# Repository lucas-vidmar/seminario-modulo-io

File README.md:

# Módulo Input / Output (I/O) para entornos educativos

> **Autores:**
> - [Lucas Vidmar](https://github.com/lucas-vidmar)
> - [Joaquín Bergmann](https://github.com/JoacoBerg)
> - [Lucas Boiero](https://github.com/boierito)
>
> **Institución:**
> - [Universidad Argentina de la Empresa (UADE)](https://www.uade.edu.ar/)

## Descripción

Este proyecto consiste en un módulo de entrada/salida (I/O) para entornos educativos, que permite a los estudiantes interactuar con sensores y actuadores a través de una interfaz gráfica de usuario (GUI) en un navegador web. El módulo I/O se comunica con el microcontrolador a través de una interfaz I2C, y proporciona una API RESTful para controlar los pines GPIO, los convertidores analógico-digital (ADC) y digital-analógico (DAC), y los codificadores rotatorios.

## Diseño de hardware

### Pinout

| Label | GPIO | Input/Output | Pines utilizados | Modo  |
|-------|------|--------------|------------------|-------|
| D2    | 2    | I/O          | Pantalla         | CS    |
| D4    | 4    | I/O          | PWM              | PWM   |
| D5    | 5    | I/O          | PWM              | PWM   |
| D12   | 12   | I/O          | Encoder          | CLK   |
| D13   | 13   | I/O          | Encoder          | DT    |
| D14   | 14   | I/O          | Encoder          | SW    |
| D15   | 15   | I/O          | DO               | DO    |
| RX2   | 16   | I/O          | U2_RXD           | U2_RXD|
| TX2   | 17   | I/O          | U2_TXD           | U2_TXD|
| D18   | 18   | I/O          | Pantalla         | SCK   |
| D19   | 19   | I/O          | Pantalla         | MISO  |
| D21   | 21   | I/O          | I2C              | SDA   |
| D22   | 22   | I/O          | I2C              | SLC   |
| D23   | 23   | I/O          | Pantalla         | MOSI  |
| D26   | 26   | I/O          | DI               | DI    |
| D27   | 27   | I/O          | DI               | DI    |
| D32   | 32   | I/O          | DO               | DO    |
| D33   | 33   | I/O          | DO               | DO    |
| D34   | 34   | I            | ADC interno      | ADC   |
| D35   | 35   | I            | ADC interno      | ADC   |
| VP    | 36   | I            | DI               | DI    |

### [Esquemático](kicad/Modulo%20IO%20Seminario.kicad_sch)

### [PCB](kicad/Modulo%20IO%20Seminario.kicad_pcb)

## Documentación de código

### [main.h](include/main.h)
Este archivo contiene las declaraciones principales del proyecto, incluidas las declaraciones de funciones para los manejadores de HTML, la impresión de menús, la lógica FSM y el control de GPIO.

### [led.h](include/led.h)
Este archivo contiene la declaración de la clase `BuiltInLed`, que proporciona métodos para controlar el LED incorporado en un microcontrolador.

### [lcdsim.h](include/lcdsim.h)
Este archivo contiene la declaración de la clase `SimulatedLCD`, que simula una pantalla LCD para fines de prueba.

### [i2c.h](include/i2c.h)
Este archivo contiene la declaración de la clase `I2C`, que proporciona métodos para inicializar la interfaz I2C y realizar operaciones de lectura y escritura en el bus I2C.

### [gpio.h](include/gpio.h)
Este archivo contiene la declaración de la clase `GPIO` y sus clases derivadas `DigitalGPIO` y `AnalogGPIO`, que proporcionan métodos para configurar, leer y escribir en los pines GPIO.

### [encodersim.h](include/encodersim.h)
Este archivo contiene la declaración de la clase `SimulatedEncoder`, que simula un codificador para fines de prueba.

### [encoder.h](include/encoder.h)
Este archivo contiene la declaración de la clase `Encoder`, que proporciona métodos para interactuar con un codificador rotatorio.

### [dac.h](include/dac.h)
Este archivo contiene la declaración de la clase `DAC`, que proporciona métodos para inicializar y controlar un Convertidor Digital a Analógico (DAC) a través de I2C.

### [adc.h](include/adc.h)
Este archivo contiene la declaración de la clase `ADC`, que proporciona métodos para interactuar con un Convertidor Analógico a Digital (ADC) a través de I2C.

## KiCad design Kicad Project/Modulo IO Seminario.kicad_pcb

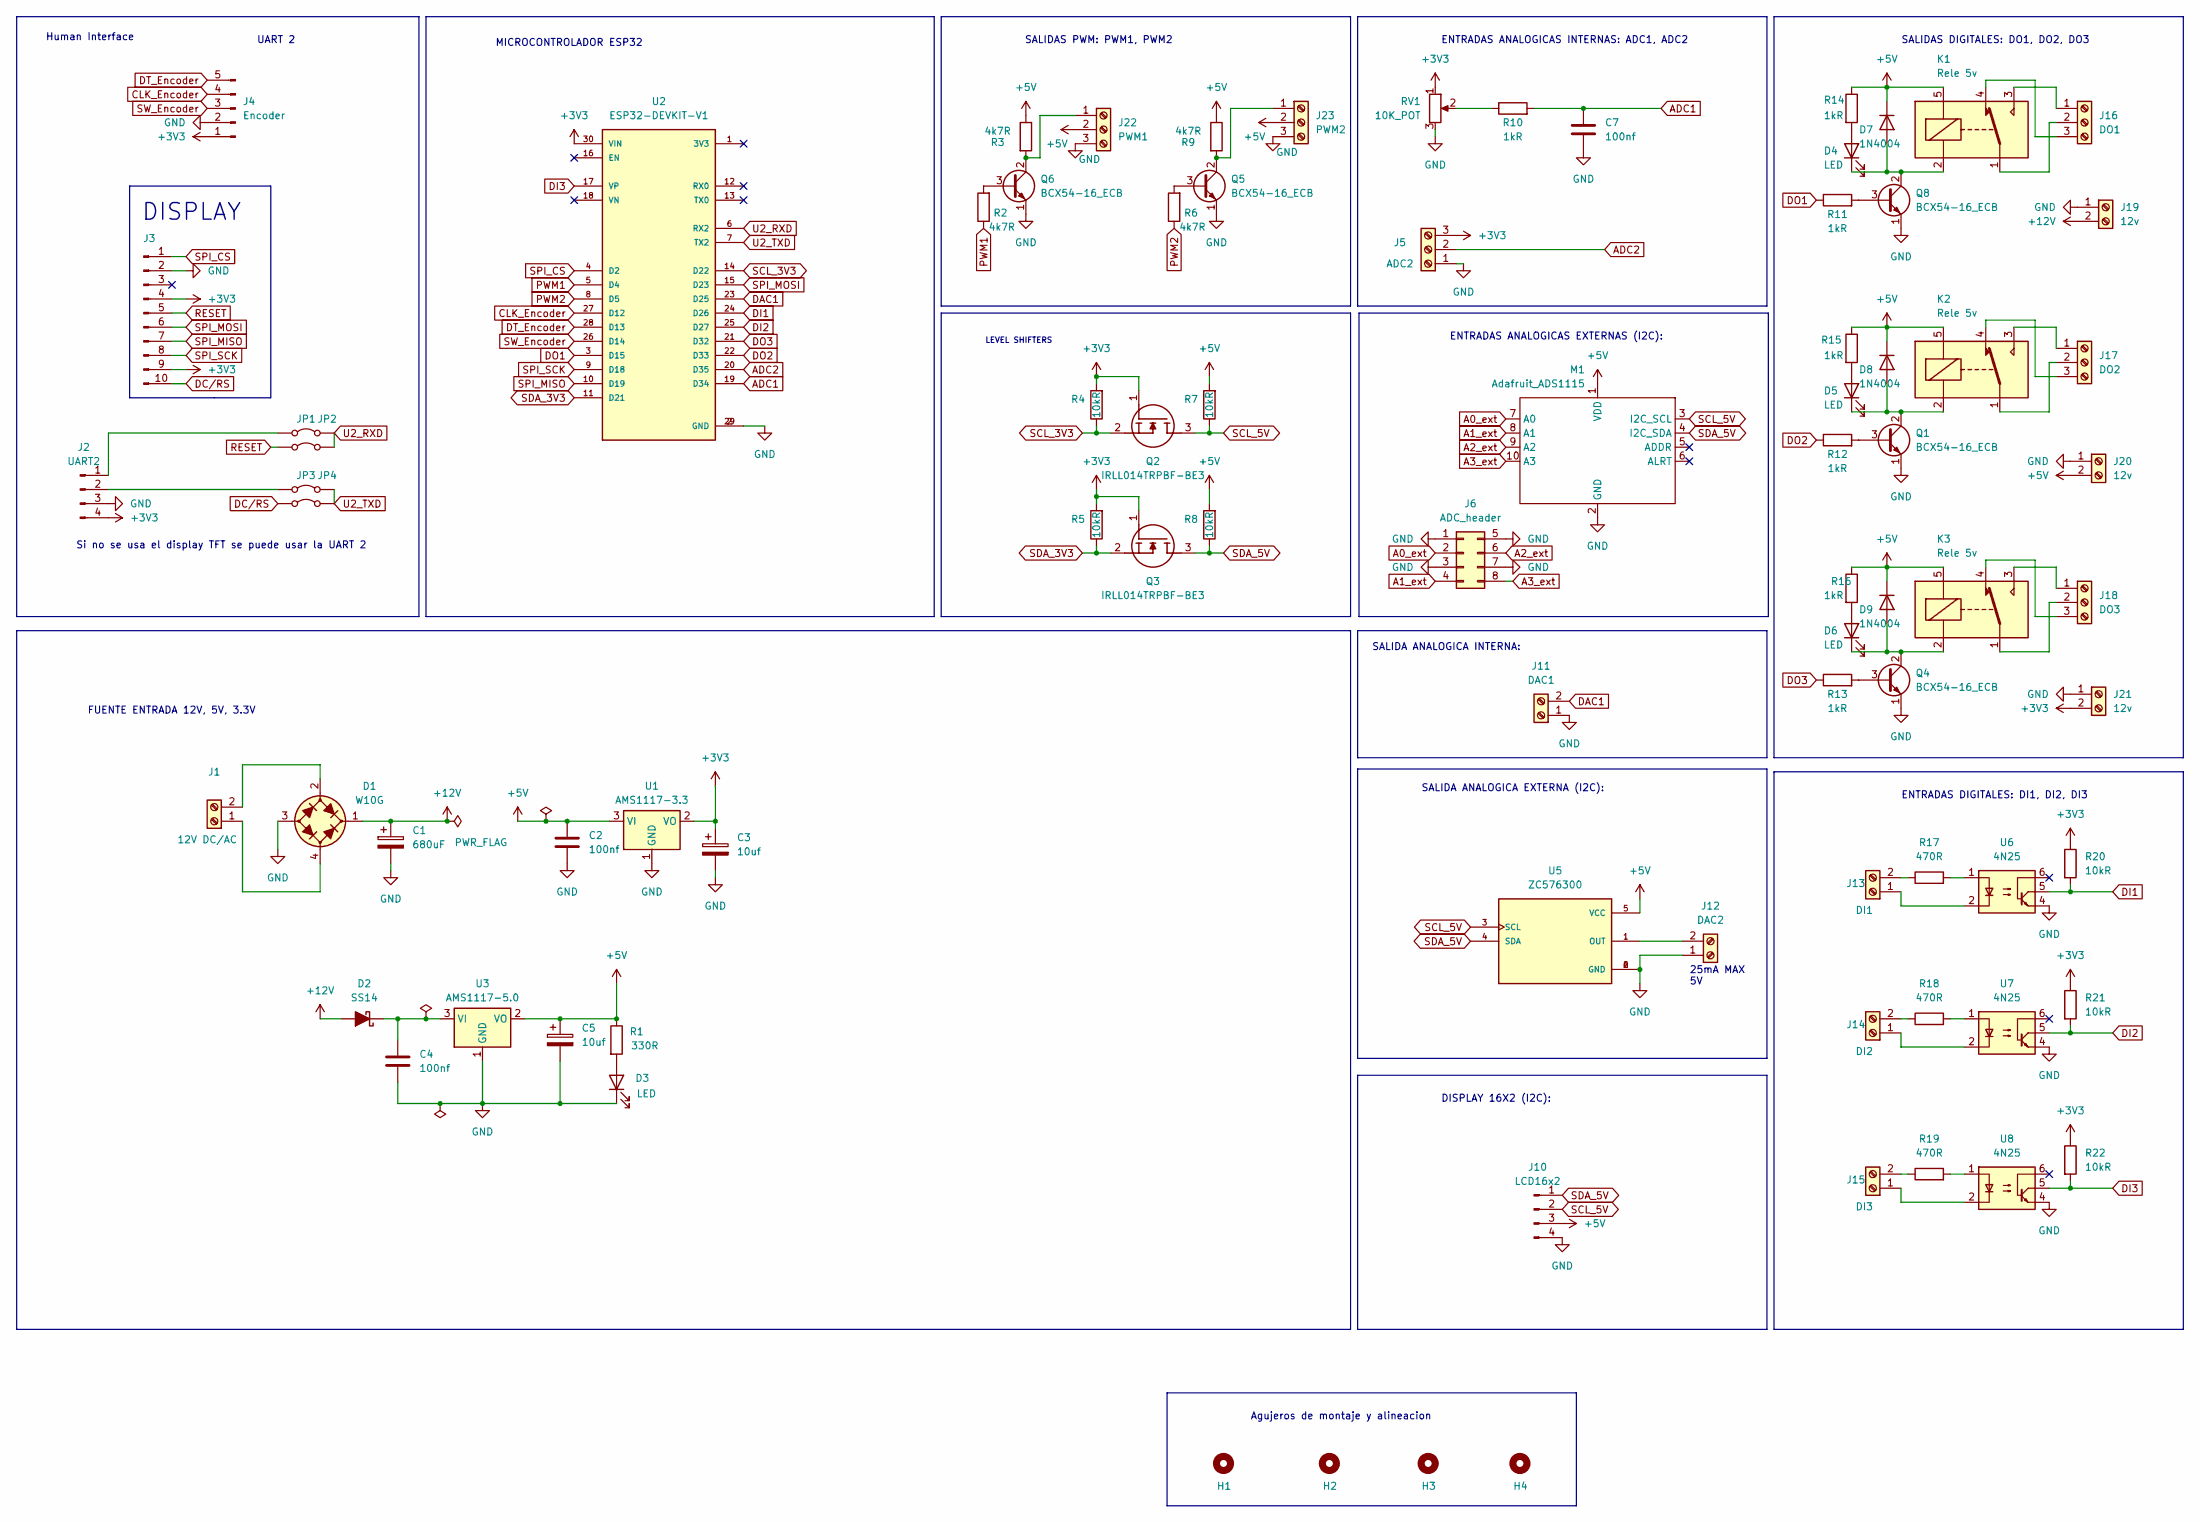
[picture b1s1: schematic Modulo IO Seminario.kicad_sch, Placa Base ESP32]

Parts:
C1: 680uF; CP_Radial_D8.0mm_P3.80mm
C2, C4, C7: 100nf; C_1812_4532Metric_Pad1.57x3.40mm_HandSolder; Mouser 18123C104JAT2A
C3, C5: 10uf; C_1812_4532Metric_Pad1.57x3.40mm_HandSolder; Mouser 1812YC106MAT2A
D1: W10G; Diode_Bridge_Round_D9.8mm
D2: SS14; D_SMA_Handsoldering; Mouser SS14
D3, D4, D5, D6: LED; led3mm
D7, D8, D9: 1N4004; D_DO-41_SOD81_P10.16mm_Horizontal
H1, H2, H3, H4: MountingHole_2.1mm
J1: 12V DC/AC; TerminalBlock_bornier-2_P5.08mm
J2: UART2; PinHeader_1.4_large
J3: Conn_01x10_Pin; CONN-TH_10P-P2.54_B10B-XADSS-N-LF-SN; Mfg Part # B10B-XADSS-N(LF)(SN); LCSC Part # C160278
J4: Encoder; PinHeader_1.5large
J5: ADC2; PinHeader_1.3_large
J6: ADC_header; PinHeader_2x04_custom
J10: LCD16x2; PinHeader_1.4_large
J11: DAC1; PinHeader_1.2_large
J12: DAC2; PinHeader_1.2_large
J13: DI1; PinHeader_1.2_large
J14: DI2; PinHeader_1.2_large
J15: DI3; PinHeader_1.2_large
J16: DO1; TerminalBlock_bornier-3_P5.08mm
J17: DO2; TerminalBlock_bornier-3_P5.08mm
J18: DO3; TerminalBlock_bornier-3_P5.08mm
J19, J20, J21: 12v; TerminalBlock_bornier-2_P5.08mm
J22: PWM1; PinHeader_1.3_large
J23: PWM2; PinHeader_1.3_large
JP1, JP2, JP3, JP4: Jumper_2_Bridged; PinHeader_1.2_large
K1, K2, K3: Rele 5v; Relay_SPDT_SANYOU_SRD_Series_Form_C
M1: Adafruit_ADS1115
Q1, Q4, Q5, Q6, Q8: BCX54-16_ECB; SOT-89_Custom; Mouser BCX54-16,115
Q2, Q3: IRLL014TRPBF-BE3; SOT-223_Custom; LCSC Part # C82045
R1: 330R; R_1210_3225Metric_Pad1.30x2.65mm_HandSolder; Mouser CRCW1210330RFKEAHP
R2, R3, R6, R9: 4k7R; R_1210_3225Metric_Pad1.30x2.65mm_HandSolder; Mouser CRCW12104K70JNEAIF
R4, R5, R7, R8: 10kR; R_1210_3225Metric_Pad1.30x2.65mm_HandSolder; Tolerancia 5%; Mfg Part # RT0805BRD0710KL; LCSC Part # C110775
R10, R11, R12, R13, R14, R15, R16: 1kR; R_1210_3225Metric_Pad1.30x2.65mm_HandSolder; Mouser CRCW12101K00JNEAIF
R17, R18, R19: 470R; R_1210_3225Metric_Pad1.30x2.65mm_HandSolder; Mouser CRCW1210470RFKEAHP
R20, R21, R22: 10kR; R_1210_3225Metric_Pad1.30x2.65mm_HandSolder; Mfg Part # RT0805BRD0710KL; Mouser CRCW121010K0JNEAIF
RV1: 10K_POT; PoteBourns
U1: AMS1117-3.3; SOT-223-3_TabPin2; Mouser LM1117MPX-3.3/NOPB
U2: ESP32-DEVKIT-V1; ESP_Test; PARTREV N/A
U3: AMS1117-5.0; SOT-223-3_TabPin2; Mouser LM1117MPX-5.0/NOPB
U5: ZC576300; MODULE_ZC576300; PARTREV v14
U6, U7, U8: 4N25; DIP-6_W7.62mm_LongPads; Mouser 4N25

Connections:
+3V3: C3.1, J2.4, J3.4, J3.9, J4.1, J5.3, J21.2, Q2.1 (G), Q3.1 (G), R4.2, R5.2, R20.1, R21.1, R22.1, RV1.1, U1.2 (VO), U2.30 (VIN)
+5V: C2.1, C5.1, D7.1 (K), D8.1 (K), D9.1 (K), J10.3, J20.2, J22.2, J23.2, K1.5, K2.5, K3.5, M1.1 (VDD), R1.1, R3.1, R7.2, R8.2, R9.1, R14.1, R15.1, R16.1, U1.3 (VI), U3.2 (VO), U5.5 (VCC)
+12V: C1.1, D1.1 (+), D2.2 (A), J19.2
A0_ext: J6.2, M1.7 (A0)
A1_ext: J6.4, M1.8 (A1)
A2_ext: J6.6, M1.9 (A2)
A3_ext: J6.8, M1.10 (A3)
ADC1: C7.1, R10.2, U2.19 (D34)
ADC2: J5.2, U2.20 (D35)
CLK_Encoder: J4.4, U2.27 (D12)
DAC1: J11.2, U2.23 (D25)
DC/RS: J3.10, JP4.1 (A)
DI1: R20.2, U2.24 (D26), U6.5
DI2: R21.2, U2.25 (D27), U7.5
DI3: R22.2, U2.17 (VP), U8.5
DO1: R11.1, U2.3 (D15)
DO2: R12.1, U2.22 (D33)
DO3: R13.1, U2.21 (D32)
DT_Encoder: J4.5, U2.28 (D13)
GND: C1.2, C2.2, C3.2, C4.2, C5.2, C7.2, D1.3 (-), D3.1 (K), J2.3, J3.2, J4.2, J5.1, J6.1, J6.3, J6.5, J6.7, J10.4, J11.1, J12.1, J19.1, J20.1, J21.1, J22.3, J23.3, M1.2 (GND), Q1.1 (E), Q4.1 (E), Q5.1 (E), Q6.1 (E), Q8.1 (E), RV1.3, U1.1 (GND), U2.2 (GND), U2.29 (GND), U3.1 (GND), U5.2 (GND), U5.6 (GND), U6.4, U7.4, U8.4
unnamed: D1.2 (1), J1.2
unnamed: D1.4 (2), J1.1
unnamed: C4.1, D2.1 (K), U3.3 (VI)
unnamed: D3.2 (A), R1.2
unnamed: D4.2 (A), R14.2
unnamed: D4.1 (K), D7.2 (A), K1.2, Q8.2 (C)
unnamed: D5.2 (A), R15.2
unnamed: D5.1 (K), D8.2 (A), K2.2, Q1.2 (C)
unnamed: D6.2 (A), R16.2
unnamed: D6.1 (K), D9.2 (A), K3.2, Q4.2 (C)
unnamed: J2.1, JP1.1 (A)
unnamed: J2.2, JP3.1 (A)
unnamed: J12.2, U5.1 (OUT)
unnamed: J13.1, U6.2
unnamed: J13.2, R17.1
unnamed: J14.1, U7.2
unnamed: J14.2, R18.1
unnamed: J15.1, U8.2
unnamed: J15.2, R19.1
unnamed: J16.1, K1.3
unnamed: J16.2, K1.1
unnamed: J16.3, K1.4
unnamed: J17.1, K2.3
unnamed: J17.2, K2.1
unnamed: J17.3, K2.4
unnamed: J18.1, K3.3
unnamed: J18.2, K3.1
unnamed: J18.3, K3.4
unnamed: J22.1, Q6.2 (C), R3.2
unnamed: J23.1, Q5.2 (C), R9.2
unnamed: Q1.3 (B), R12.2
unnamed: Q4.3 (B), R13.2
unnamed: Q5.3 (B), R6.2
unnamed: Q6.3 (B), R2.2
unnamed: Q8.3 (B), R11.2
unnamed: R10.1, RV1.2
unnamed: R17.2, U6.1
unnamed: R18.2, U7.1
unnamed: R19.2, U8.1
PWM1: R2.1, U2.5 (D4)
PWM2: R6.1, U2.8 (D5)
RESET: J3.5, JP2.1 (A)
SCL_3V3: Q2.2 (S), R4.1, U2.14 (D22)
SCL_5V: J10.2, M1.3 (I2C_SCL), Q2.3 (D), R7.1, U5.3 (SCL)
SDA_3V3: Q3.2 (S), R5.1, U2.11 (D21)
SDA_5V: J10.1, M1.4 (I2C_SDA), Q3.3 (D), R8.1, U5.4 (SDA)
SPI_CS: J3.1, U2.4 (D2)
SPI_MISO: J3.7, U2.10 (D19)
SPI_MOSI: J3.6, U2.15 (D23)
SPI_SCK: J3.8, U2.9 (D18)
SW_Encoder: J4.3, U2.26 (D14)
U2_RXD: JP1.2 (B), JP2.2 (B), U2.6 (RX2)
U2_TXD: JP3.2 (B), JP4.2 (B), U2.7 (TX2)

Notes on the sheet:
SALIDA ANALOGICA INTERNA:
UART 2
Si no se usa el display TFT se puede usar la UART 2
Agujeros de montaje y alineacion
25mA MAX 5V
MICROCONTROLADOR ESP32
ENTRADAS DIGITALES: DI1, DI2, DI3
DISPLAY 16X2 (I2C):
SALIDA ANALOGICA EXTERNA (I2C):
ENTRADAS ANALOGICAS INTERNAS: ADC1, ADC2
FUENTE ENTRADA 12V, 5V, 3.3V
ENTRADAS ANALOGICAS EXTERNAS (I2C):
Human Interface
SALIDAS DIGITALES: DO1, DO2, DO3
LEVEL SHIFTERS
DISPLAY
SALIDAS PWM: PWM1, PWM2

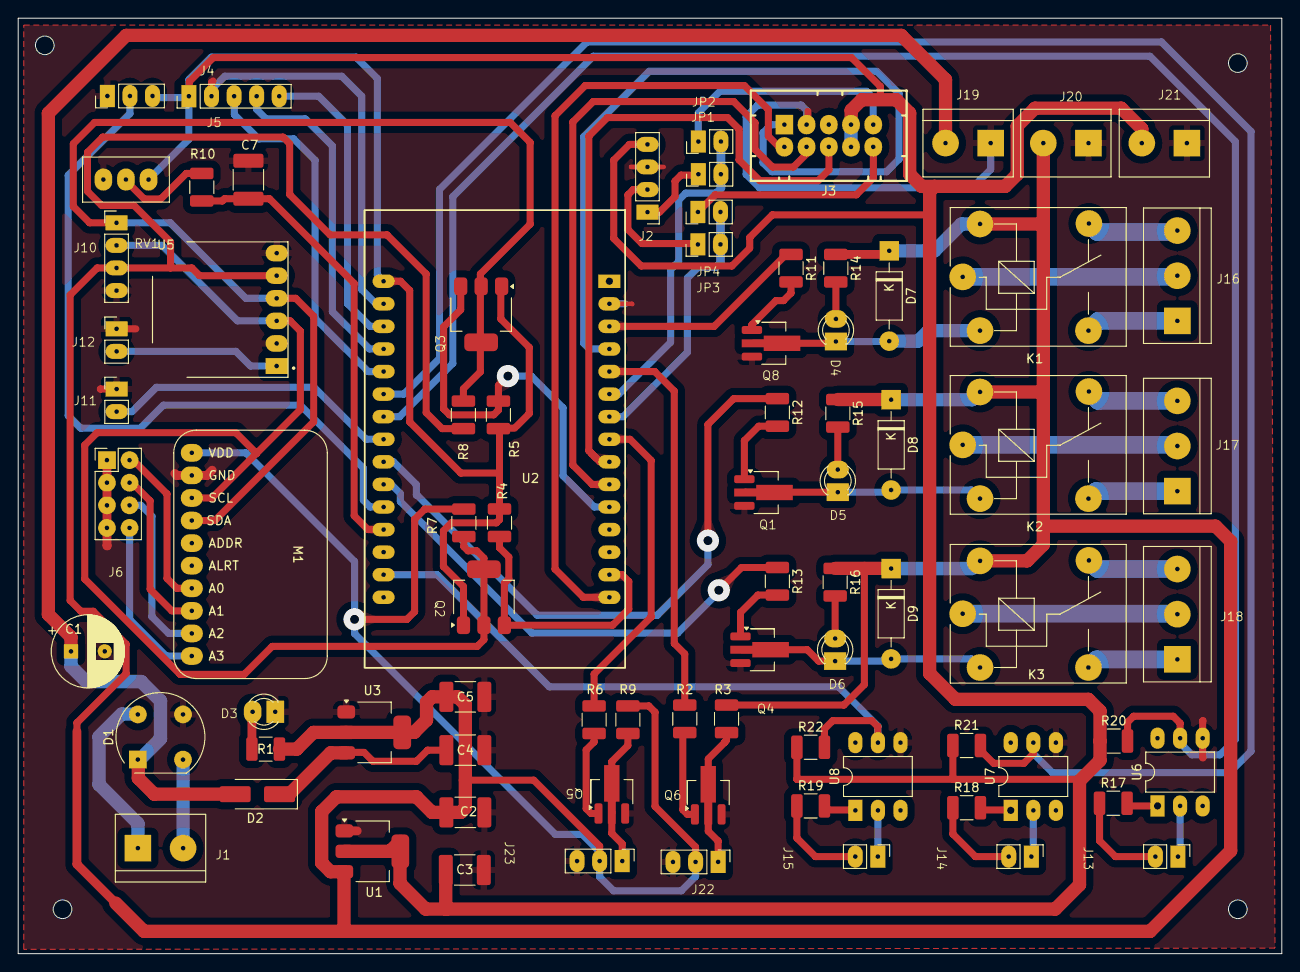
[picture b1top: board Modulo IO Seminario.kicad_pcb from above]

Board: 2 copper layers, 142.2 x 105.2 mm, 84 parts (0 on the bottom side), 73 nets.

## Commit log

2024-11-26 basic html working
2024-11-26 html interface working
2024-11-27 encoder y lcd simulado
2024-11-27 encoder simulado ajustado y menu de mediciones
2024-11-27 starting control menu
2024-11-27 Digital control working
2024-11-28 adjustment 1
2024-11-28 adjustment 2
2024-11-28 Adding analog control
2024-11-29 adjustment 3
2024-11-29 adjustment 4
2024-11-29 adjustment 5
2024-11-30 adjustment 6
2024-11-30 pwm working
2024-11-30 adjustments on encoder usage
2024-11-30 dac working via interface
2024-11-30 screen working
2024-11-30 adjustment 7
2024-11-30 adjustment 8
2024-11-30 adjustment 9
2024-11-30 header file doc
2024-11-30 src file doc
2024-11-30 Rename README to README.md
2024-11-30 starting readme
2024-11-30 better doc
2024-11-30 kicad project
2024-11-30 kicad
2024-12-02 adjustment 10
2024-12-02 adjustment 11
